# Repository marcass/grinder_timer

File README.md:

# grinder_timer
timer switch for coffee grinder
* Adjustable time for grind or grind on demand
* LCD display
* small circuit board for mounting inside grinder chasis

## Timer adjustment
* Option for rotary encoder
* Option for potentiometer

### Rotary encoder

* Useful for user defined adjustment steps (eg 50ms or 100ms)
* Setup a little trickier
* https://forum.arduino.cc/index.php?topic=242356.0 FOR ROATRY ENCODER
* https://github.com/0xPIT/encoder/tree/arduino
* https://www.circuitsathome.com/mcu/reading-rotary-encoder-on-arduino/

### Potentiometer

* Easy setup
* Timer value will change with heat of potentiometer
* Increments depend on temp and potentiometer used
* Using 10k pot

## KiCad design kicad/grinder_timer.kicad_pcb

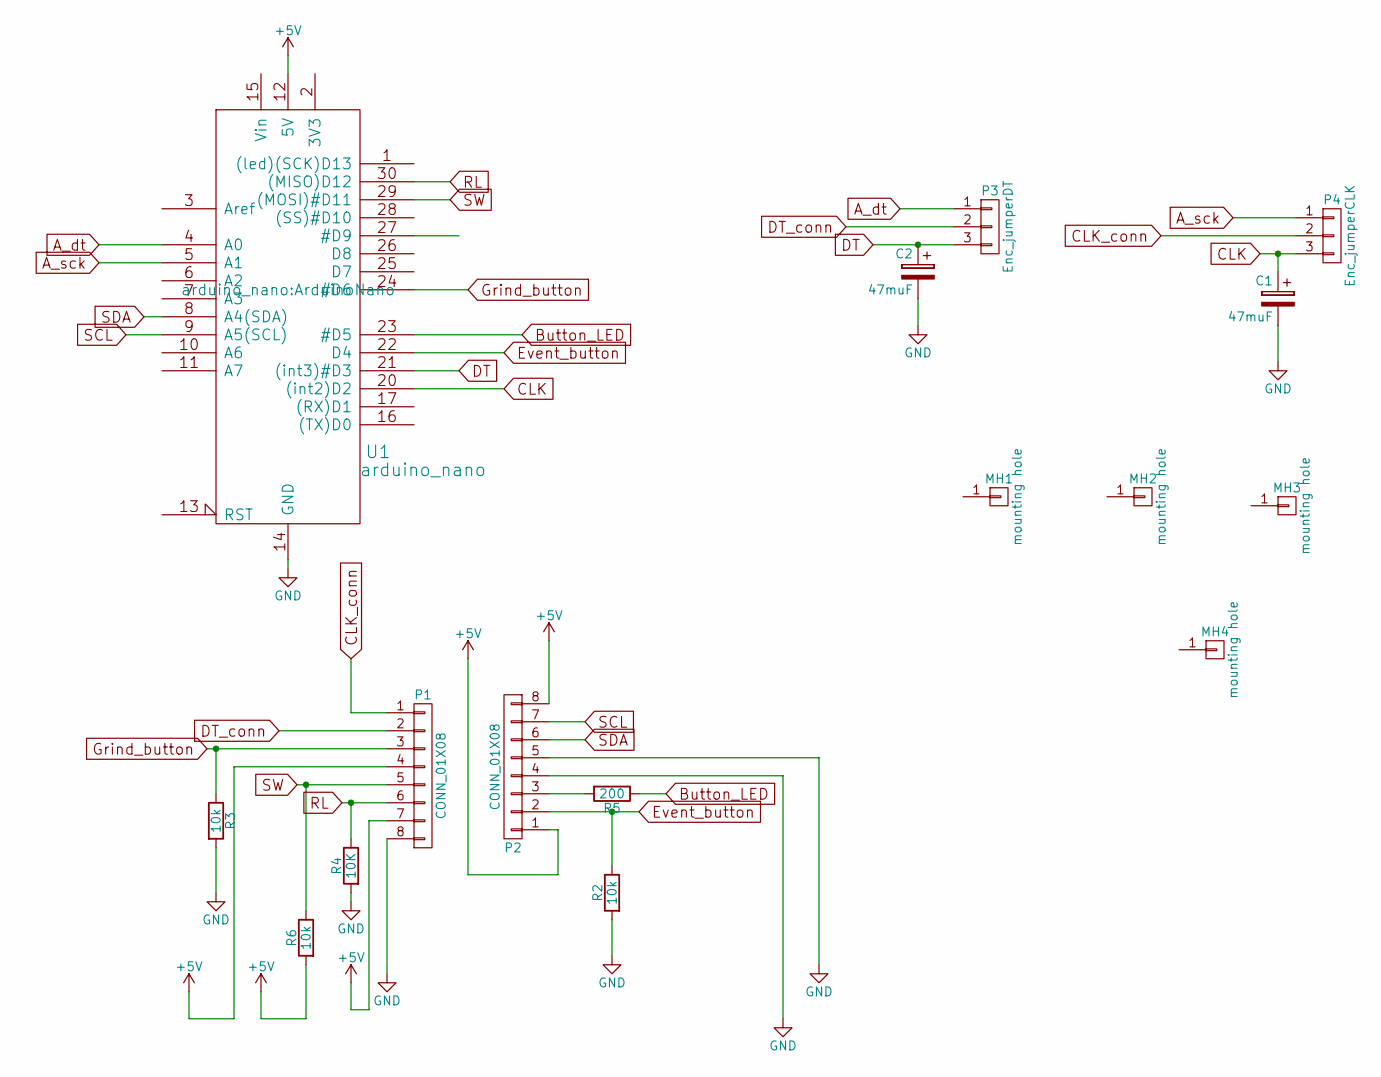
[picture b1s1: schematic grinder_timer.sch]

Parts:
C1, C2: 47muF; CP_Radial_D10.0mm_P3.50mm
MH1, MH2, MH3, MH4: mounting hole; MountingHole_3.2mm_M3_DIN965_Pad
P1, P2: CONN_01X08; PhoenixContact_MCV-G_08x3.50mm_Vertical
P3: Enc_jumperDT; Pin_Header_Straight_1x03
P4: Enc_jumperCLK; Pin_Header_Straight_1x03
R2, R3, R6: 10k; R_Axial_DIN0207_L6.3mm_D2.5mm_P10.16mm_Horizontal
R4: 10K; R_Axial_DIN0207_L6.3mm_D2.5mm_P10.16mm_Horizontal
R5: 200; R_Axial_DIN0207_L6.3mm_D2.5mm_P10.16mm_Horizontal
U1: arduino_nano; ArduinoNano

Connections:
+5V: P1.4, P1.7, P2.1, P2.8, R6.2, U1.12 (5V)
A_dt: P3.1, U1.4 (A0)
A_sck: P4.1, U1.5 (A1)
Button_LED: R5.1, U1.23 (#D5)
CLK: C1.1, P4.3, U1.20 ((int2)D2)
CLK_conn: P1.1, P4.2
DT: C2.1, P3.3, U1.21 ((int3)#D3)
DT_conn: P1.2, P3.2
Event_button: P2.2, R2.1, U1.22 (D4)
GND: C1.2, C2.2, P1.8, P2.4, P2.5, R2.2, R3.2, R4.2, U1.14 (GND), U1.19 (GND)
Grind_button: P1.3, R3.1, U1.24 (#D6)
unnamed: P2.3, R5.2
RL: P1.6, R4.1, U1.30 ((MISO)D12)
SCL: P2.7, U1.9 (A5(SCL))
SDA: P2.6, U1.8 (A4(SDA))
SW: P1.5, R6.1, U1.29 ((MOSI)#D11)

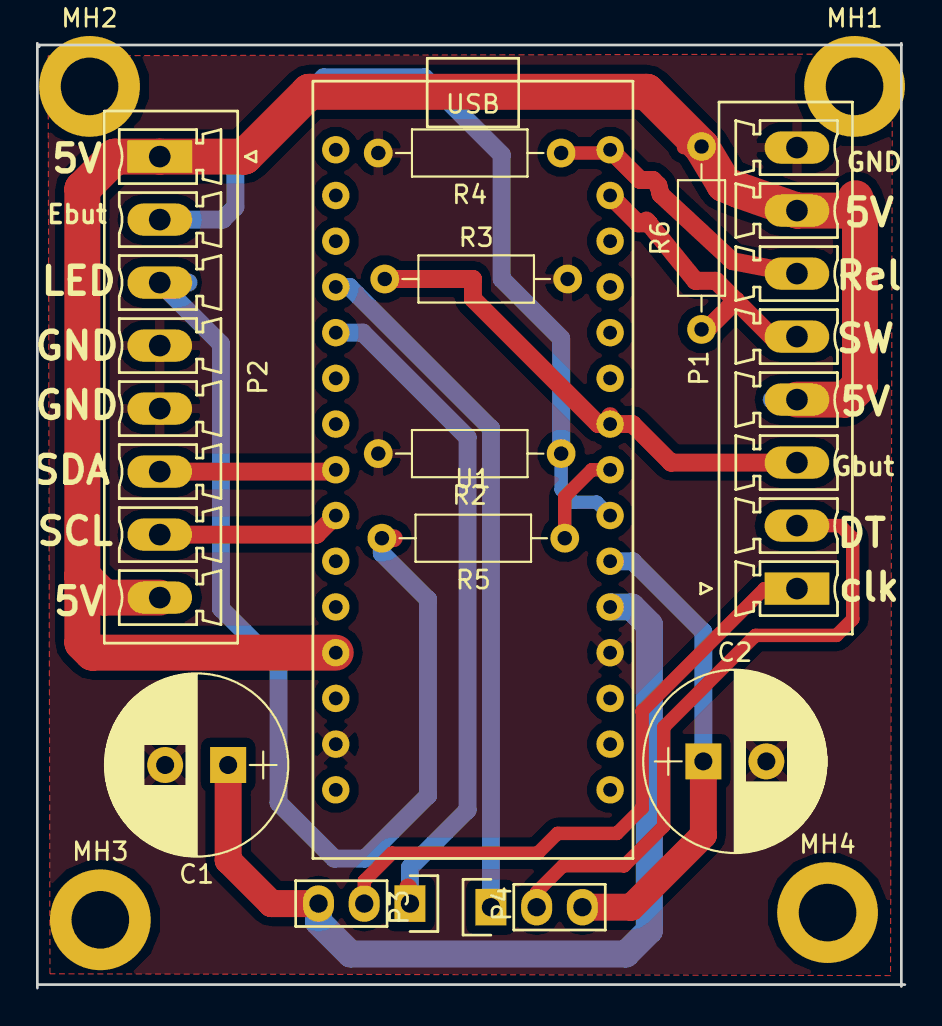
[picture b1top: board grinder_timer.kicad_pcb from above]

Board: 2 copper layers, 48.2 x 52.5 mm, 16 parts (0 on the bottom side), 16 nets.

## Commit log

2017-01-23 frist commit
2017-01-23 added potentiaometer for adjusting grind time (not tested)
2017-01-23 added lcd, changed var names
2017-01-23 Placed mode button. Need to finish later
2017-01-24 tidied up on demand mode
2017-01-24 added relay for neutral, updated to active low relays and tidied logic
2017-01-26 button logic continues....
2017-01-26 fixed logic issues on switches
2017-01-26 solved some issues, cannot get state to gho form demand to timer and vice versa as varialbe event_press not being updated
2017-01-26 Working now. To do: relays on startup and LCD updates
2017-01-27 Tidied up variables
2017-01-27 Fixed logic issues. Check relays then build!
2017-01-27 fixed relays starting on startup (was connected to pin 13)
2017-01-28 UPdated LCD stuff
2017-01-28 Changed grind state stuff
2017-01-29 PWM for LED button
2017-01-29 fucked around with everything
2017-01-29 working with some dodgy workarounds
2017-01-31 changed grind timer form interrupt to button press in loop
2017-02-01 Update LCD scrren update on grinding in demand
2017-02-01 Pulled mode change out of interrupt and into button read
2017-02-01 Cleaned up and attempted fix for failed event interrupt
2017-02-01 Updated grind_time variable to volatile and set in isr
2017-02-02 new fix for poor timer after cancel performance
2017-02-02 new new fix for poor timer after cancel performance
2017-02-02 bool test for grinder timer start
2017-02-02 bool test for grinder timer start adn more variable manip
2017-02-02 ... adn more variable manip
2017-02-02 ...and more variable manip
2017-02-02 fix for swithing modes timer failure initially
2017-02-02 changed debounce variabls for mode change
2017-02-02 fix for swithing modes timer failure initially. again
2017-02-02 fix for swithing modes timer failure initially. again..
2017-02-03 fix for swithing modes timer failure initially. again...
2017-02-03 interrupts chnaged again
2017-02-03 interrupt flags set
2017-02-03 remove all double refs to interrupts
2017-02-05 removed final interrupt
2017-02-05 tidied up
2017-02-18 Remove neutral switching
2017-02-18 added kicad
2017-02-20 updated sketch for rotary encoder read in loop
2017-02-25 Added preset storage
2017-02-26 added sensible preset for eeprom
2017-02-26 fiddled with rot encoder reader
2017-03-08 changed pin assignments. NOT PWM PIN IN PCB DAMNIT
2017-03-08 modified sketch to give pwm
2017-03-11 updated for newly arrived rotary encoder
2017-03-11 added logic for wrting to eeprom
2017-03-12 got the encoder working and displaying
2019-05-03 added adaptor for hopper attachment
2019-05-06 fucking around wiht cad
2019-05-06 got some holes
2019-05-08 final design, now need to do paths
2019-05-08 trying to slice
2019-05-09 fiddling with path
2019-05-10 getting cutting paths sorted slowly
2019-05-17 fucknig aroudn with patsh
2019-05-24 fucking free cad
2019-05-29 plastic coupling
2019-05-29 plastic hopper stuff
2019-05-30 updated grider adaptor
2019-05-30 rm surplus files
2019-05-30 updated for oled display
2019-05-31 weird adaptive profiling cut
2019-07-21 oled testing
2019-07-22 working oled display
2019-08-10 rationlised files and updated display
